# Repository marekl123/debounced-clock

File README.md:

# debounced-clock

Best to be used with KiCad 4.0.5

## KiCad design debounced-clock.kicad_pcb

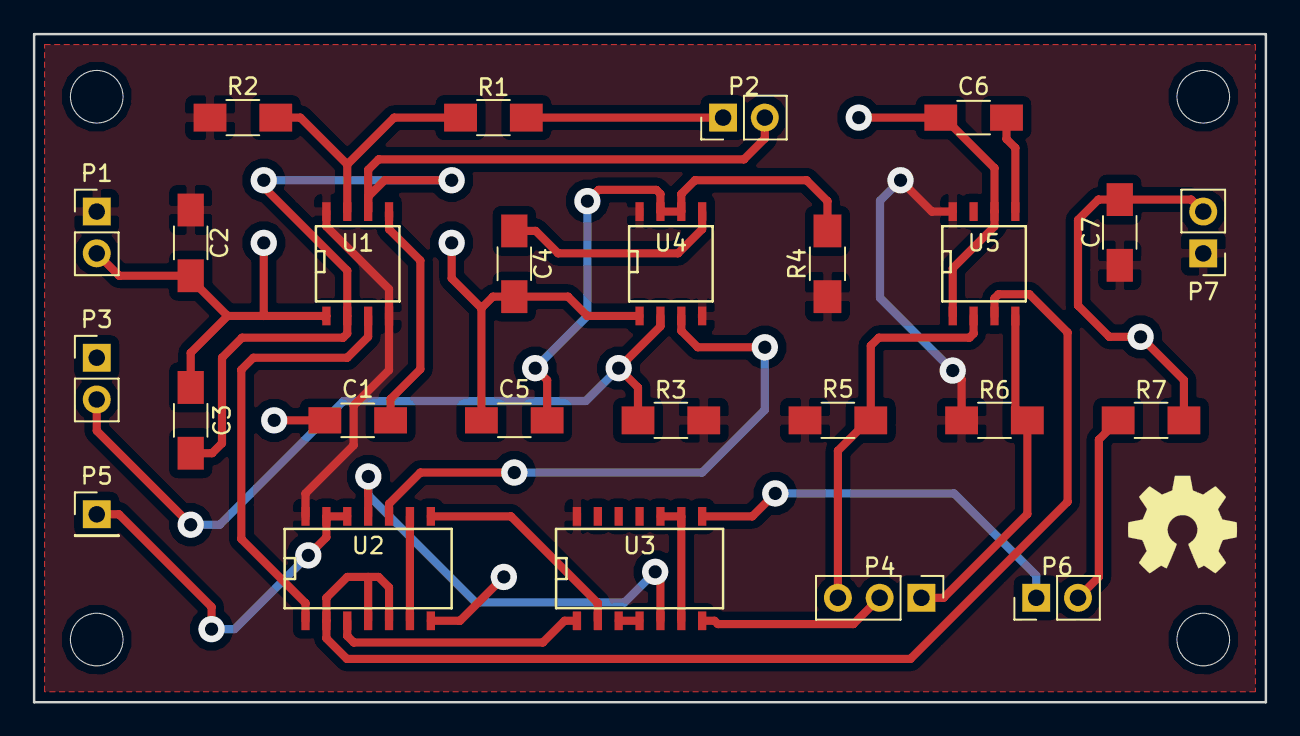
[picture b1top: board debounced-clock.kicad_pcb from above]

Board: 2 copper layers, 74.9 x 40.6 mm, 26 parts (0 on the bottom side), 24 nets.

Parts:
C1, C2, C4, C6, C7: 0.01uF; C_1206_HandSoldering
C3: 1uF; C_1206_HandSoldering
C5: 0.1uF; C_1206_HandSoldering
P1, P7: POWER; Pin_Header_Straight_1x02_Pitch2.54mm
P2: POT; Pin_Header_Straight_1x02_Pitch2.54mm
P3: STEP; Pin_Header_Straight_1x02_Pitch2.54mm
P4: SWITCH; Pin_Header_Straight_1x03_Pitch2.54mm
P5: HALT; Pin_Header_Straight_1x01_Pitch2.54mm
P6: LED; Pin_Header_Straight_1x02_Pitch2.54mm
R1, R2, R3, R5, R6: 1K; R_1206_HandSoldering
R4: 1M; R_1206_HandSoldering
R7: 220; R_1206_HandSoldering
U1, U4, U5: NE555; SOIC-8-N
U2, U3: 7400; SOIC-14_N

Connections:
GND: C1.2, C2.2, C3.2, C4.2, C5.2, C6.2, C7.2, P1.2, P3.1, P4.2, P7.2, R7.2, U1.1, U2.7, U3.7, U4.1, U5.1, U5.6
HALT: P5.1, U2.12, U2.13
unnamed: C1.1, U1.5
unnamed: C4.1, U4.5
unnamed: C5.1, R4.2, U4.6, U4.7
unnamed: C6.1, U5.5
unnamed: P2.1, R1.2
unnamed: P3.2, R3.1, U4.2
unnamed: P4.1, R6.2, U5.4
unnamed: P4.3, R5.1, U5.2
unnamed: P6.1, U3.8
unnamed: P6.2, R7.1
unnamed: R1.1, R2.1, U1.7
unnamed: U2.3, U3.1
unnamed: U2.6, U2.9
unnamed: U2.8, U3.2
unnamed: U2.11, U3.5
unnamed: U3.3, U3.4
unnamed: U3.6, U3.9, U3.10
OUTPUT_AS: U1.3, U2.1
OUTPUT_MS: U2.10, U4.3
SELECT: U2.2, U2.4, U2.5, U5.3
TRIGGER: C3.1, P2.2, U1.2, U1.6
VCC: C2.1, C7.1, P1.1, P7.1, R2.2, R3.2, R4.1, R5.2, R6.1, U1.4, U1.8, U2.14, U3.14, U4.4, U4.8, U5.8

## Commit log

2021-03-06 Schematics/PCB fix, Via size change, OSH logo moved to silk layer
